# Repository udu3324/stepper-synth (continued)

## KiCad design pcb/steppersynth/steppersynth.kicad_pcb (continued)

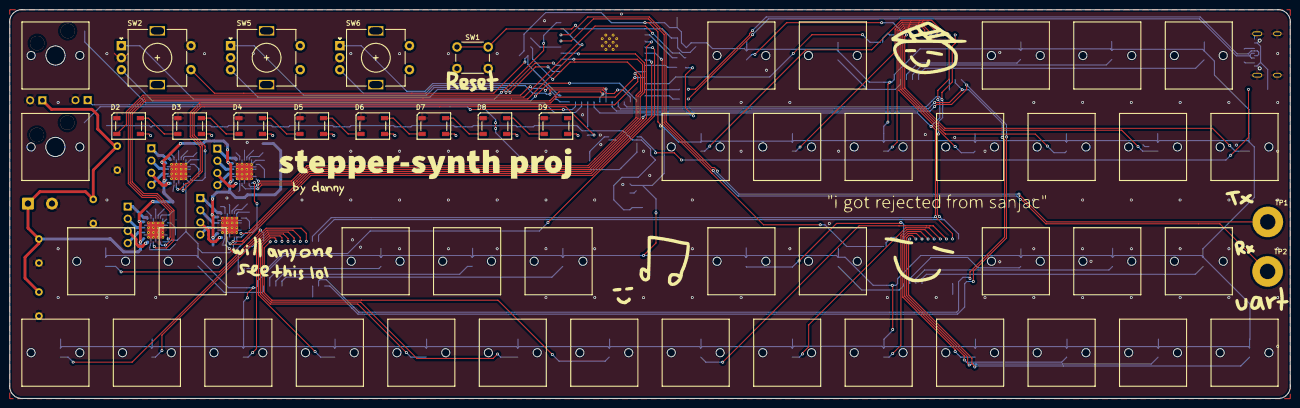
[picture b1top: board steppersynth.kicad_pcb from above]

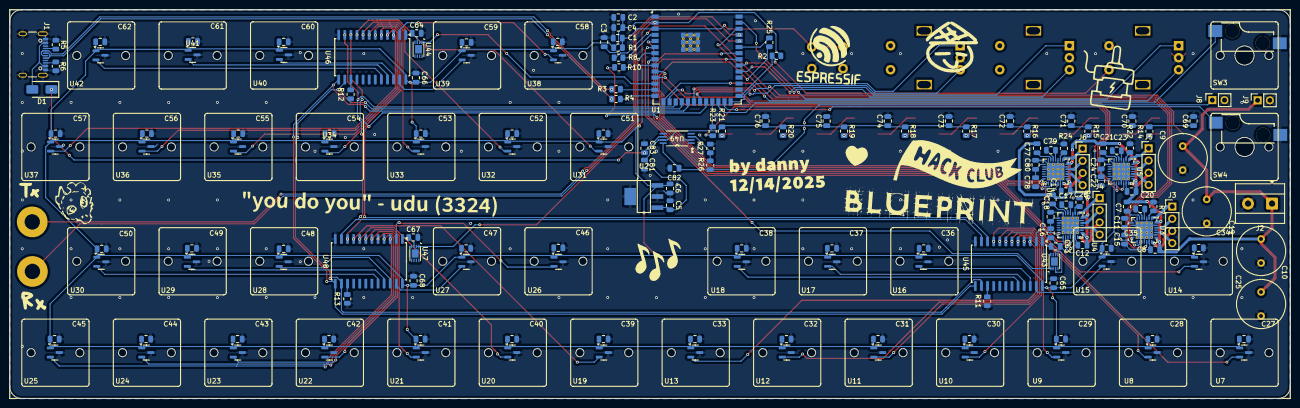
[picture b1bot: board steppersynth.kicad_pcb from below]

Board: 2 copper layers, 266.7 x 81.0 mm, 184 parts (170 on the bottom side), 143 nets.

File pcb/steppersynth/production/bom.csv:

Designator,Footprint,Quantity,Value,LCSC Part #
C1,0805,1,1uF,
"C10, C19, C25, C9",C_Radial_D10.0mm_H12.5mm_P5.00mm,4,150µF,
"C11, C16, C22, C78",0805,4,2.2µF,
"C12, C14, C20, C21, C26, C63, C64, C65, C66, C67, C68, C69, C7, C70, C71, C72, C73, C74, C75, C76, C77, C8",0805,22,100nF,
"C13, C17, C23, C79",0805,4,22nF,
"C15, C18, C24, C80, C81",0805,5,4.7µF,
C2,0805,1,10μF,
"C27, C28, C29, C30, C31, C32, C33, C34, C35, C36, C37, C38, C39, C40, C41, C42, C43, C44, C45, C46, C47, C48, C49, C50, C51, C52, C53, C54, C55, C56, C57, C58, C59, C60, C61, C62",0805,36,0.01µF,
"C3, C4, C82, C83",0805,4,0.1μF,
C5,0805,1,0.47μF,
C6,0805,1,47μF,
D1,D_SMA,1,SS14,
"D2, D3, D4, D5, D6, D7, D8, D9",LED_WS2812B_PLCC4_5.0x5.0mm_P3.2mm,8,WS2812B,
J1,USB_C_Receptacle_GCT_USB4105-xx-A_16P_TopMnt_Horizontal,1,USB4105,
J2,TerminalBlock_MetzConnect_Type055_RT01502HDWU_1x02_P5.00mm_Horizontal,1,LRS-350-24,
"J3, J4, J5, J6",PinHeader_1x04_P2.54mm_Vertical,4,Conn_01x04_Pin,
J8,PinSocket_1x02_P2.54mm_Vertical,1,Conn_01x02_Pin,
J9,PinSocket_1x02_P2.54mm_Vertical,1,Conn_01x02_Socket,
"R1, R11, R12, R13, R2, R26",0805,6,10kΩ,
"R10, R23, R25, R8",0805,4,1kΩ,
"R14, R15, R16, R17, R18, R19, R20, R21",0805,8,220Ω,
"R22, R24, R7, R9",0805,4,20kΩ,
R27,0805,1,100kΩ,
"R3, R4",0805,2,0Ω,
"R5, R6",0805,2,5.1kΩ,
SW1,SW_PUSH_6mm,1,SW_SPST,
"SW2, SW5, SW6",RotaryEncoder_Alps_EC11E-Switch_Vertical_H20mm,3,RotaryEncoder_Switch,
"SW3, SW4",TH_L10.9-W5.9-CPG151101S11,2,SW_Push_45deg,
"TP1, TP2",MountingHole_3.2mm_M3_Pad,2,TestPoint,
U1,ESP32-S3-WROOM-2,1,ESP32-S3-WROOM-2,
"U10, U11, U12, U13, U14, U15, U16, U17, U18, U19, U20, U21, U22, U23, U24, U25, U26, U27, U28, U29, U30, U31, U32, U33, U34, U35, U36, U37, U38, U39, U40, U41, U42, U7, U8, U9",SOT-23,36,DRV5055A3xDBZxQ1,
U2,SOT-223-4_L6.5-W3.5-P2.30-LS7.0-BR,1,LM3940IMPX-3.3/NOPB,C544820
"U3, U4, U5, U6",VQFN-28-1EP_5x5mm_P0.5mm_EP3.7x3.7mm_ThermalVias,4,TMC2209-LA,
"U43, U44, U47",DFN-8-1EP_3x2mm_P0.5mm_EP1.75x1.45mm,3,MCP6002-xMC,
"U45, U46, U48",SOIC-24W_7.5x15.4mm_P1.27mm,3,CD74HC4067M,
U49,PW8,1,TPS2115APW,

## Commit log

2025-12-04 add kicad files + more
2025-12-07 update kicad stuff
2025-12-07 fix tmc motor stuff + more
2025-12-08 position everything in the pcb
2025-12-09 dc-dc buck converter
2025-12-13 fix some pcb layout stuff
2025-12-14 finish tracing everything
2025-12-15 add journal, readme, cad, and assets
2025-12-15 fix missing image
2025-12-15 add divinikey and mouser totals
2025-12-15 add more prices
2025-12-15 add new cart
2025-12-15 add sample firmware
2025-12-31 add libs and all pinout devices
